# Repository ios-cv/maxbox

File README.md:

MaxBox open-source hardware
====================

This repository is for the 3D design files, KiCad PCB design/Gerber files, and ESP-IDF firmware files to produce a MaxBox control box. This takes the form of a 100mm diameter circular PCB with a Mifare antenna, buck converter capable of up to 36V DC input, RGB LEDs, high speed CAN bus transceiver, an ESP32-WROVER castellated module incorporating a Bluetooth and WiFi antenna, and GPIO to connect buttons and relays.

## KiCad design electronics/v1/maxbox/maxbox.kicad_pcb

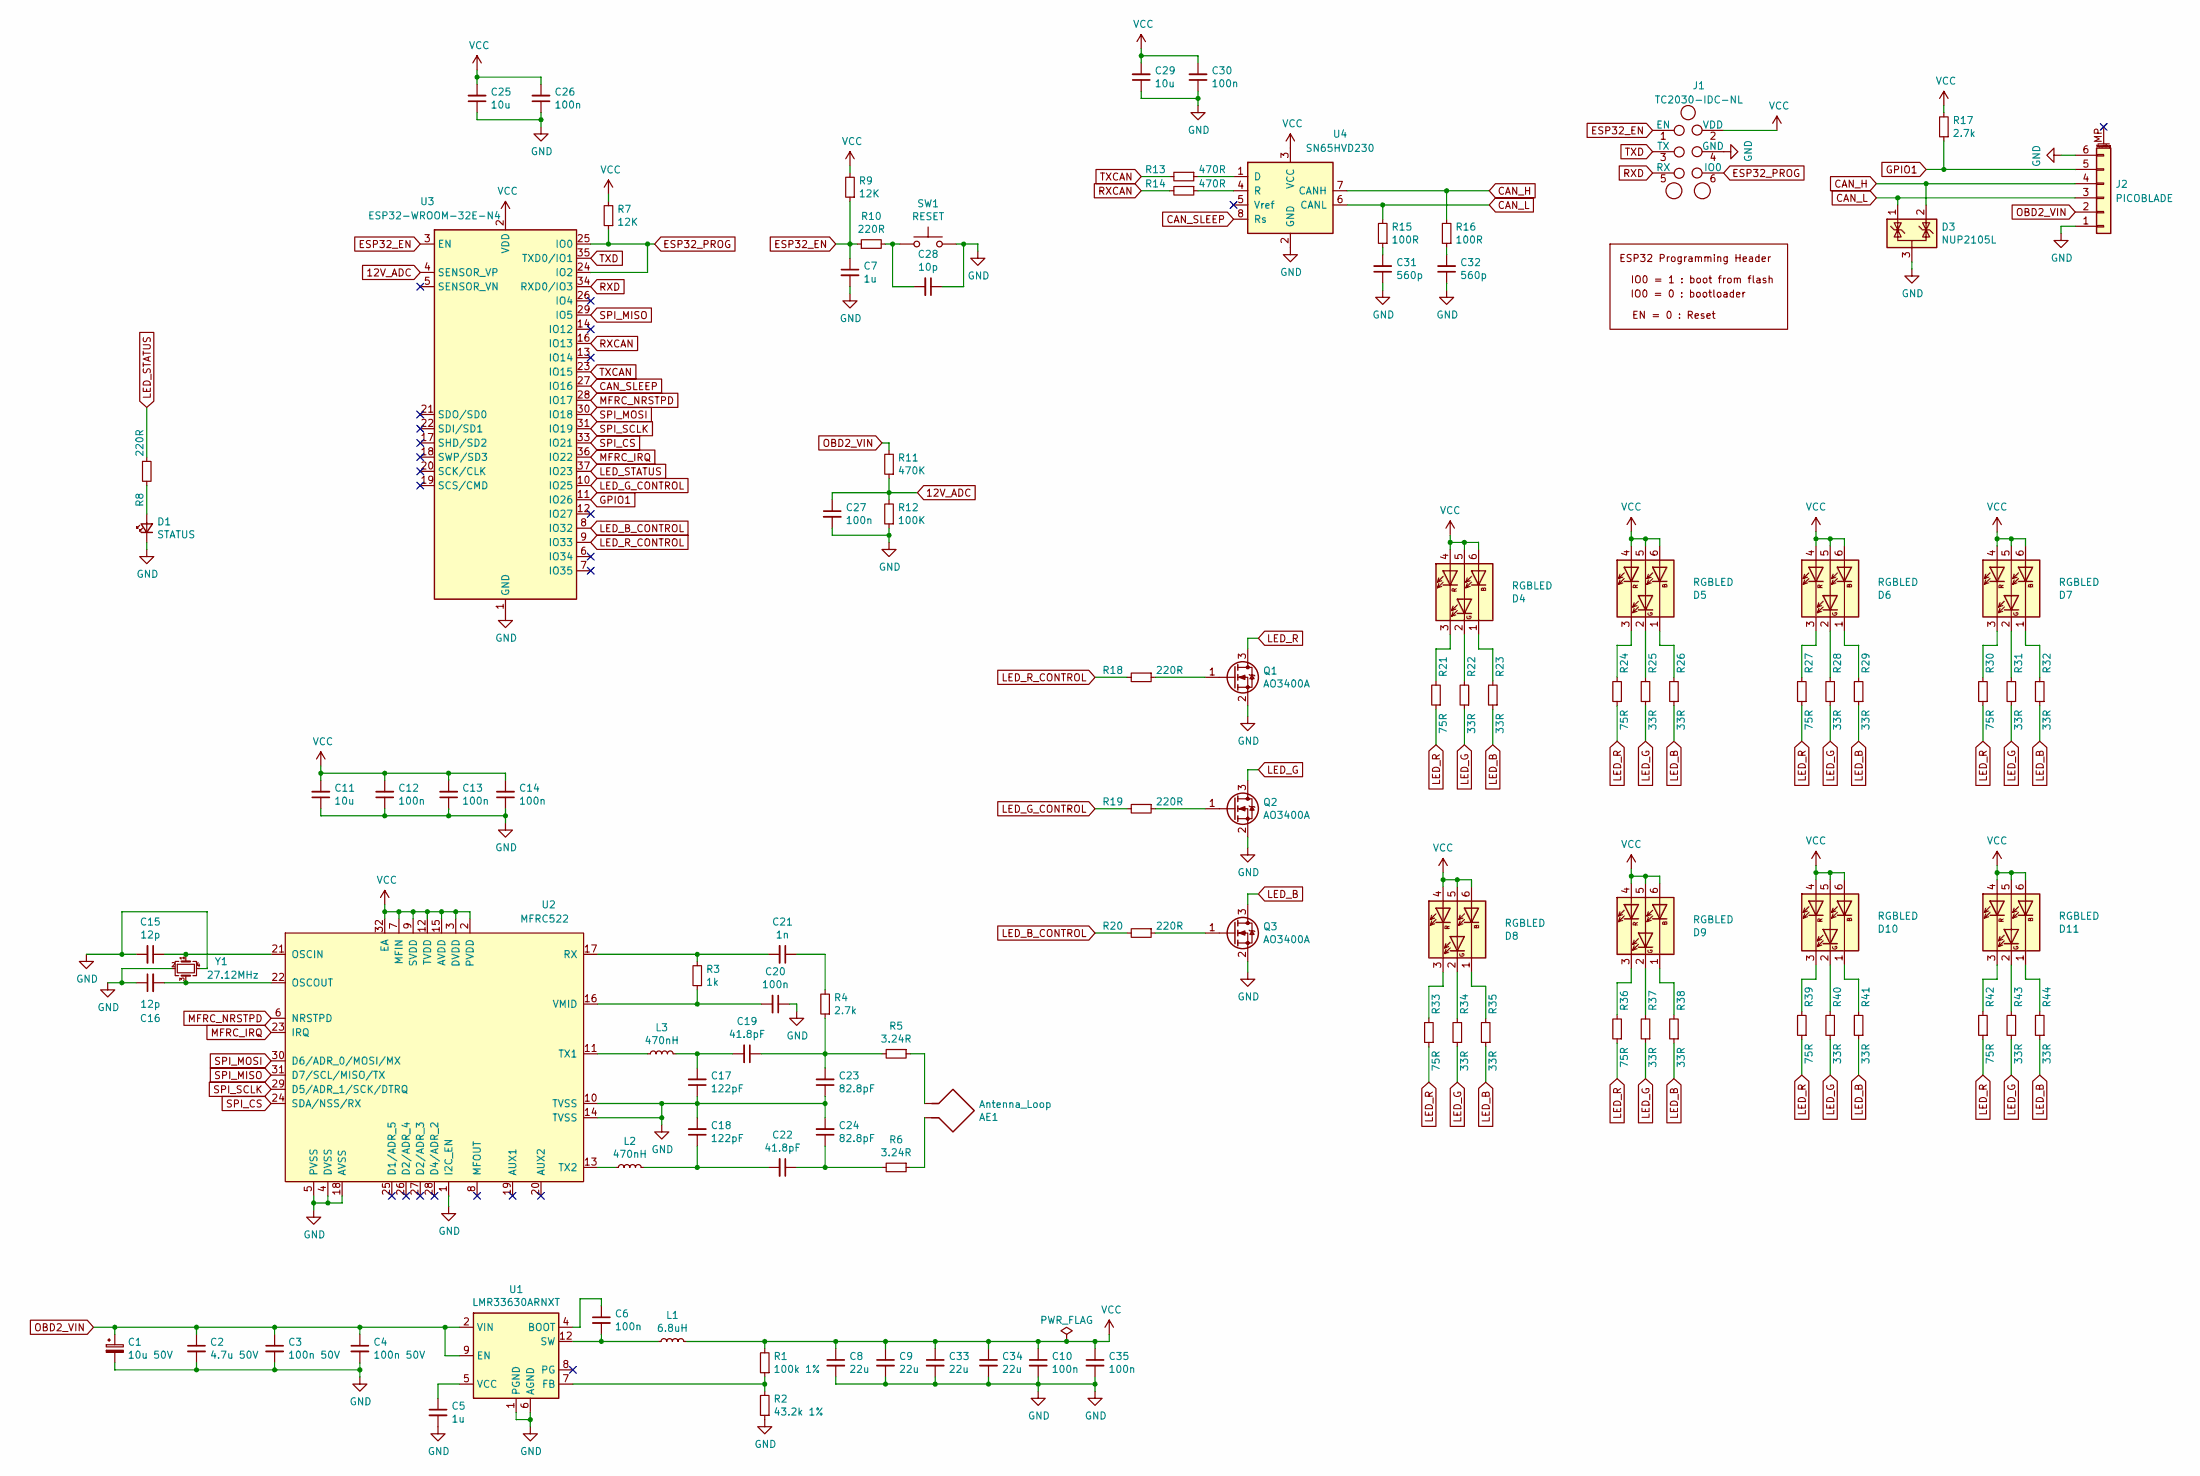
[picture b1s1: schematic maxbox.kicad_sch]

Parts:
AE1: Antenna_Loop; 95mm-3turn-antenna
C1: 10u 50V; C_0805_2012Metric; LCSC C440198
C2: 4.7u 50V; C_1206_3216Metric; LCSC C29823
C3, C4: 100n 50V; C_0402_1005Metric; LCSC C307331
C5, C7: 1u; C_0402_1005Metric; LCSC C52923
C6, C10, C12, C13, C14, C20, C26, C27, C30, C35: 100n; C_0402_1005Metric; LCSC C307331
C8, C9, C33, C34: 22u; C_0805_2012Metric; LCSC C45783
C11, C25, C29: 10u; C_0402_1005Metric; LCSC C15525
C15, C16: 12p; C_0805_2012Metric; LCSC C1792
C17, C18: 122pF; C_0603_1608Metric; LCSC C18438
C19, C22: 41.8pF; C_0805_2012Metric; LCSC C502147
C21: 1n; C_0402_1005Metric; LCSC C1523
C23, C24: 82.8pF; C_0805_2012Metric; LCSC C105942
C28: 10p; C_0402_1005Metric; LCSC C32949
C31, C32: 560p; C_0402_1005Metric; LCSC C1537
D1: STATUS; LED_0603_1608Metric; LCSC C72043
D3: NUP2105L; SOT-23; LCSC C284104
D4, D5, D6, D7, D8, D9, D10, D11: RGBLED; LED_FM-Z2727RGBA-SH; LCSC C727905
J1: TC2030-IDC-NL_ESP; Tag-Connect_TC2030-IDC-NL_2x03_P1.27mm_Vertical
J2: PICOBLADE; Molex_PicoBlade_53261-0671_1x06-1MP_P1.25mm_Horizontal; LCSC C99277
L1: 6.8uH; L_Cenker_CKST0603; LCSC C3002639
L2, L3: 470nH; L_0805_2012Metric; LCSC C655211
Q1, Q2, Q3: AO3400A; SOT-23; LCSC C20917
R1: 100k 1%; R_0402_1005Metric; LCSC C25741
R2: 43.2k 1%; R_0603_1608Metric; LCSC C23172
R3: 1k; R_0402_1005Metric; LCSC C11702
R4, R17: 2.7k; R_0603_1608Metric; LCSC C13167
R5, R6: 3.24R; R_0402_1005Metric; LCSC C270612
R7, R9: 12K; R_0402_1005Metric; LCSC C25752
R8, R10, R18, R19, R20: 220R; R_0402_1005Metric; LCSC C25091
R11: 470K; R_0402_1005Metric; LCSC C25790
R12: 100K; R_0402_1005Metric; LCSC C25741
R13, R14: 470R; R_0402_1005Metric; LCSC C25117
R15, R16: 100R; R_0402_1005Metric; LCSC C25076
R21, R24, R27, R30, R33, R36, R39, R42: 75R; R_0402_1005Metric; LCSC C25133
R22, R23, R25, R26, R28, R29, R31, R32, R34, R35, R37, R38, R40, R41, R43, R44: 33R; R_0402_1005Metric; LCSC C25105
SW1: RESET; XKB_TS-1187A-B-A-B; LCSC C318884
U1: LMR33630ARNXT; RNX0012B_VQFN-HR; LCSC C2861505
U2: MFRC522; VQFN-32-1EP_5x5mm_P0.5mm_EP3.5x3.5mm_ThermalVias; LCSC C11322
U3: ESP32-WROOM-32E-N4; ESP32-WROOM-32; LCSC C701341
U4: SN65HVD230; SOIC-8_3.9x4.9mm_P1.27mm; LCSC C12084
Y1: 27.12MHz; Crystal_SMD_3225-4Pin_3.2x2.5mm; LCSC C113669

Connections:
12V_ADC: C27.1, R11.1, R12.2, U3.4 (SENSOR_VP)
CAN_H: D3.2 (K), J2.4, R16.2, U4.7 (CANH)
CAN_L: D3.1 (K), J2.3, R15.2, U4.6 (CANL)
CAN_SLEEP: U3.27 (IO16), U4.8 (Rs)
ESP32_EN: C7.1, J1.1 (EN), R9.1, R10.1, U3.3 (EN)
ESP32_PROG: J1.6 (IO0), R7.1, U3.24 (IO2), U3.25 (IO0)
GND: C1.2, C2.2, C3.2, C4.2, C5.2, C7.2, C8.2, C9.2, C10.2, C11.1, C12.1, C13.1, C14.1, C15.2, C16.1, C17.1, C18.2, C20.1, C23.1, C24.2, C25.1, C26.1, C27.2, C28.1, C29.1, C30.1, C31.1, C32.1, C33.2, C34.2, C35.2, D1.1 (K), D3.3 (A), J1.4 (GND), J2.1, J2.6, Q1.2 (S), Q2.2 (S), Q3.2 (S), R2.1, R12.1, SW1.2, U1.1 (PGND), U1.6 (AGND), U1.11 (PGND), U2.1 (I2C_EN), U2.4 (DVSS), U2.5 (PVSS), U2.10 (TVSS), U2.14 (TVSS), U2.18 (AVSS), U3.1 (GND), U3.15 (GND), U3.38 (GND), U3.39 (GND), U4.2 (GND), Y1.2, Y1.4
GPIO1: J2.5, R17.1, U3.11 (IO26)
LED_B: Q3.3 (D), R23.1, R26.1, R29.1, R32.1, R35.1, R38.1, R41.1, R44.1
LED_B_CONTROL: R20.2, U3.8 (IO32)
LED_G: Q2.3 (D), R22.1, R25.1, R28.1, R31.1, R34.1, R37.1, R40.1, R43.1
LED_G_CONTROL: R19.2, U3.10 (IO25)
LED_R: Q1.3 (D), R21.1, R24.1, R27.1, R30.1, R33.1, R36.1, R39.1, R42.1
LED_R_CONTROL: R18.2, U3.9 (IO33)
LED_STATUS: R8.1, U3.37 (IO23)
MFRC_IRQ: U2.23 (IRQ), U3.36 (IO22)
MFRC_NRSTPD: U2.6 (NRSTPD), U3.28 (IO17)
unnamed: AE1.1, R6.1
unnamed: AE1.2, R5.1
unnamed: C5.1, U1.5 (VCC)
unnamed: C6.1, U1.4 (BOOT)
unnamed: C6.2, L1.1, U1.3 (NC), U1.12 (SW)
unnamed: C15.1, U2.21 (OSCIN), Y1.1
unnamed: C16.2, U2.22 (OSCOUT), Y1.3
unnamed: C17.2, C19.2, L3.2
unnamed: C18.1, C22.2, L2.2
unnamed: C19.1, C23.2, R4.1, R5.2
unnamed: C20.2, R3.1, U2.16 (VMID)
unnamed: C21.1, R4.2
unnamed: C21.2, R3.2, U2.17 (RX)
unnamed: C22.1, C24.1, R6.2
unnamed: C28.2, R10.2, SW1.1
unnamed: C31.2, R15.1
unnamed: C32.2, R16.1
unnamed: D1.2 (A), R8.2
unnamed: D4.1 (KB), R23.2
unnamed: D4.2 (KG), R22.2
unnamed: D4.3 (KR), R21.2
unnamed: D5.1 (KB), R26.2
unnamed: D5.2 (KG), R25.2
unnamed: D5.3 (KR), R24.2
unnamed: D6.1 (KB), R29.2
unnamed: D6.2 (KG), R28.2
unnamed: D6.3 (KR), R27.2
unnamed: D7.1 (KB), R32.2
unnamed: D7.2 (KG), R31.2
unnamed: D7.3 (KR), R30.2
unnamed: D8.1 (KB), R35.2
unnamed: D8.2 (KG), R34.2
unnamed: D8.3 (KR), R33.2
unnamed: D9.1 (KB), R38.2
unnamed: D9.2 (KG), R37.2
unnamed: D9.3 (KR), R36.2
unnamed: D10.1 (KB), R41.2
unnamed: D10.2 (KG), R40.2
unnamed: D10.3 (KR), R39.2
unnamed: D11.1 (KB), R44.2
unnamed: D11.2 (KG), R43.2
unnamed: D11.3 (KR), R42.2
unnamed: L2.1, U2.13 (TX2)
unnamed: L3.1, U2.11 (TX1)
unnamed: Q1.1 (G), R18.1
unnamed: Q2.1 (G), R19.1
unnamed: Q3.1 (G), R20.1
unnamed: R1.1, R2.2, U1.7 (FB)
unnamed: R13.1, U4.1 (D)
unnamed: R14.1, U4.4 (R)
OBD2_VIN: C1.1, C2.1, C3.1, C4.1, J2.2, R11.2, U1.2 (VIN), U1.9 (EN), U1.10 (VIN)
RXCAN: R14.2, U3.16 (IO13)
RXD: J1.5 (RX), U3.34 (RXD0/IO3)
SPI_CS: U2.24 (SDA/NSS/RX), U3.33 (IO21)
SPI_MISO: U2.31 (D7/SCL/MISO/TX), U3.29 (IO5)
SPI_MOSI: U2.30 (D6/ADR_0/MOSI/MX), U3.30 (IO18)
SPI_SCLK: U2.29 (D5/ADR_1/SCK/DTRQ), U3.31 (IO19)
TXCAN: R13.2, U3.23 (IO15)
TXD: J1.3 (TX), U3.35 (TXD0/IO1)
VCC: C8.1, C9.1, C10.1, C11.2, C12.2, C13.2, C14.2, C25.2, C26.2, C29.2, C30.2, C33.1, C34.1, C35.1, D4.4 (AR), D4.5 (AG), D4.6 (AB), D5.4 (AR), D5.5 (AG), D5.6 (AB), D6.4 (AR), D6.5 (AG), D6.6 (AB), D7.4 (AR), D7.5 (AG), D7.6 (AB), D8.4 (AR), D8.5 (AG), D8.6 (AB), D9.4 (AR), D9.5 (AG), D9.6 (AB), D10.4 (AR), D10.5 (AG), D10.6 (AB), D11.4 (AR), D11.5 (AG), D11.6 (AB), J1.2 (VDD), L1.2, R1.2, R7.2, R9.2, R17.2, U2.2 (PVDD), U2.3 (DVDD), U2.7 (MFIN), U2.9 (SVDD), U2.12 (TVDD), U2.15 (AVDD), U2.32 (EA), U3.2 (VDD), U4.3 (VCC)

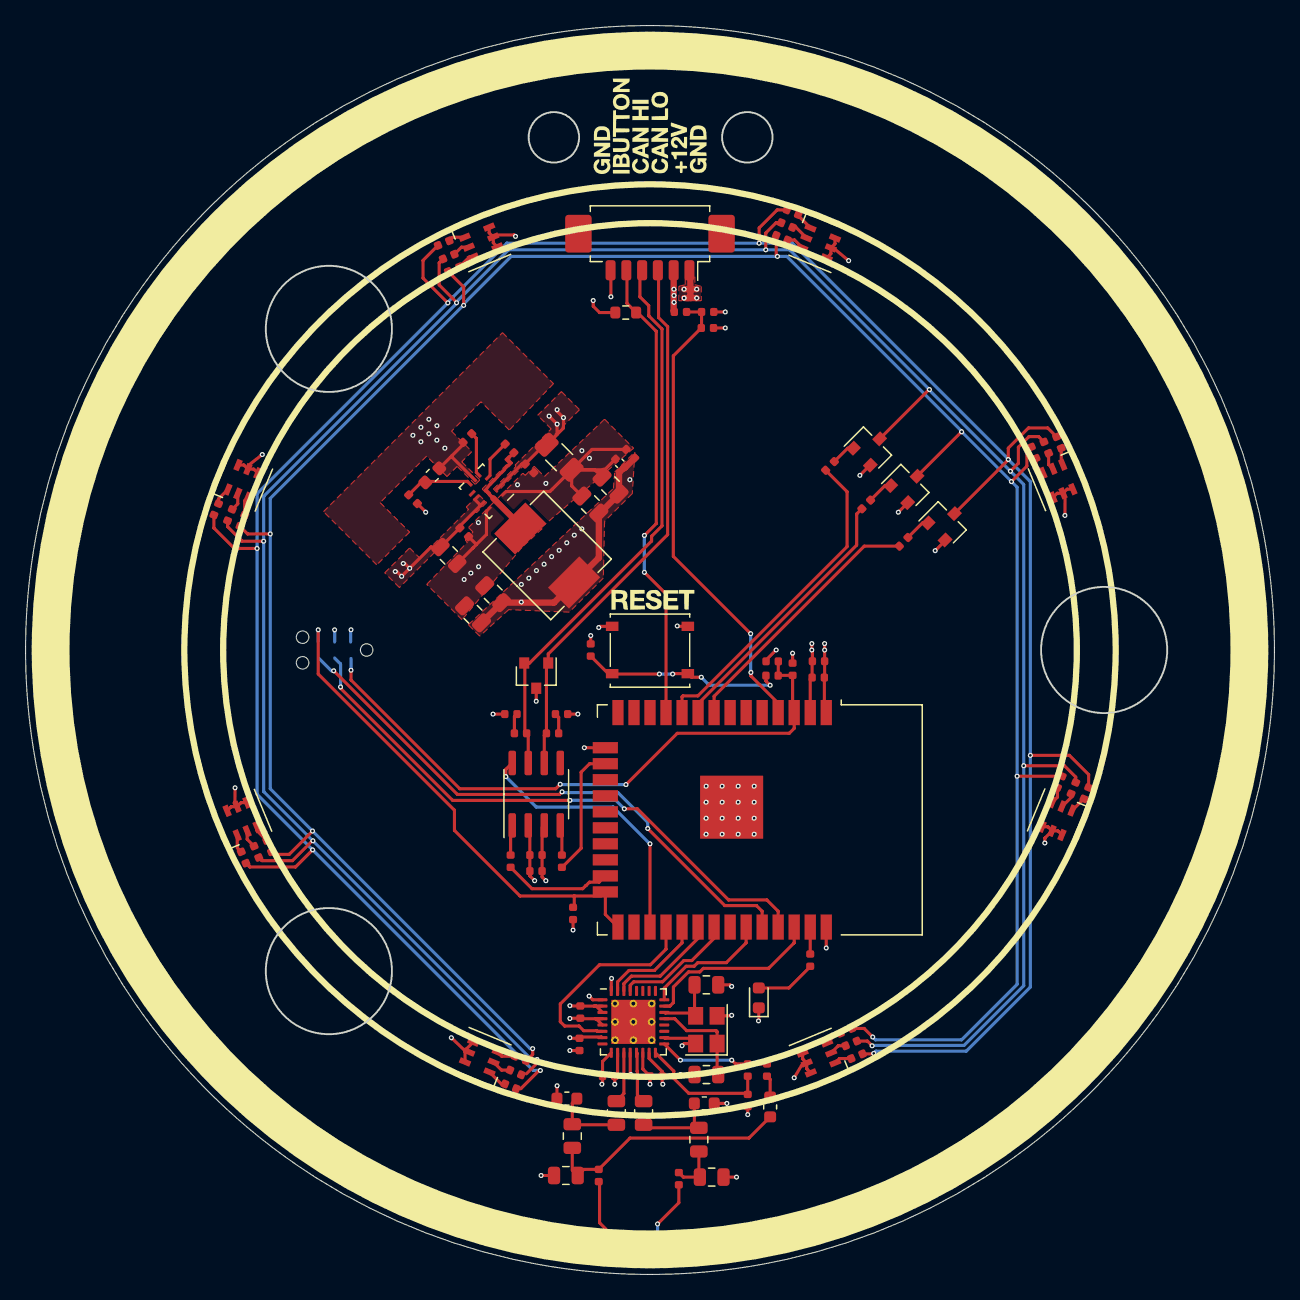
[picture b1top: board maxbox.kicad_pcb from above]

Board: 4 copper layers, 98.9 x 98.9 mm, 104 parts (1 on the bottom side), 77 nets.

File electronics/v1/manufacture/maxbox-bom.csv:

Comment,Designator,Footprint,LCSC
"10u 50V","C1","Capacitor_SMD:C_0805_2012Metric","C440198"
"10u","C11,C25,C29","Capacitor_SMD:C_0402_1005Metric","C15525"
"12p","C15,C16","Capacitor_SMD:C_0805_2012Metric","C1792"
"122pF","C17,C18","Capacitor_SMD:C_0603_1608Metric","C18438"
"41.8pF","C19,C22","Capacitor_SMD:C_0805_2012Metric","C502147"
"4.7u 50V","C2","Capacitor_SMD:C_1206_3216Metric","C29823"
"1n","C21","Capacitor_SMD:C_0402_1005Metric","C1523"
"82.8pF","C23,C24","Capacitor_SMD:C_0805_2012Metric","C105942"
"10p","C28","Capacitor_SMD:C_0402_1005Metric","C32949"
"100n 50V","C3,C4","Capacitor_SMD:C_0402_1005Metric","C307331"
"560p","C31,C32","Capacitor_SMD:C_0402_1005Metric","C1537"
"1u","C5,C7","Capacitor_SMD:C_0402_1005Metric","C52923"
"100n","C6,C10,C12,C13,C14,C20,C26,C27,C30,C35","Capacitor_SMD:C_0402_1005Metric","C307331"
"22u","C8,C9,C33,C34","Capacitor_SMD:C_0805_2012Metric","C45783"
"STATUS","D1","LED_SMD:LED_0603_1608Metric","C72043"
"NUP2105L","D3","Package_TO_SOT_SMD:SOT-23","C284104"
"RGBLED","D4,D5,D6,D7,D8,D9,D10,D11","maxlibrary:LED_FM-Z2727RGBA-SH","C727905"
"TC2030-IDC-NL_ESP","J1","Connector:Tag-Connect_TC2030-IDC-NL_2x03_P1.27mm_Vertical",""
"PICOBLADE","J2","Connector_Molex:Molex_PicoBlade_53261-0671_1x06-1MP_P1.25mm_Horizontal","C99277"
"6.8uH","L1","maxlibrary:L_Cenker_CKST0603","C3002639"
"470nH","L2,L3","Inductor_SMD:L_0805_2012Metric","C655211"
"AO3400A","Q1,Q2,Q3","Package_TO_SOT_SMD:SOT-23","C20917"
"100k 1%","R1","Resistor_SMD:R_0402_1005Metric","C25741"
"470K","R11","Resistor_SMD:R_0402_1005Metric","C25790"
"100K","R12","Resistor_SMD:R_0402_1005Metric","C25741"
"470R","R13,R14","Resistor_SMD:R_0402_1005Metric","C25117"
"100R","R15,R16","Resistor_SMD:R_0402_1005Metric","C25076"
"43.2k 1%","R2","Resistor_SMD:R_0603_1608Metric","C23172"
"75R","R21,R24,R27,R30,R33,R36,R39,R42","Resistor_SMD:R_0402_1005Metric","C25133"
"33R","R22,R23,R25,R26,R28,R29,R31,R32,R34,R35,R37,R38,R40,R41,R43,R44","Resistor_SMD:R_0402_1005Metric","C25105"
"1k","R3","Resistor_SMD:R_0402_1005Metric","C11702"
"2.7k","R4,R17","Resistor_SMD:R_0603_1608Metric","C13167"
"3.24R","R5,R6","Resistor_SMD:R_0402_1005Metric","C270612"
"12K","R7,R9","Resistor_SMD:R_0402_1005Metric","C25752"
"220R","R8,R10,R18,R19,R20","Resistor_SMD:R_0402_1005Metric","C25091"
"RESET","SW1","maxlibrary:XKB_TS-1187A-B-A-B","C318884"
"LMR33630ARNXT","U1","maxlibrary:RNX0012B_VQFN-HR","C2861505"
"MFRC522","U2","Package_DFN_QFN:VQFN-32-1EP_5x5mm_P0.5mm_EP3.5x3.5mm_ThermalVias","C11322"
"ESP32-WROOM-32E-N4","U3","RF_Module:ESP32-WROOM-32","C701341"
"SN65HVD230","U4","Package_SO:SOIC-8_3.9x4.9mm_P1.27mm","C12084"
"27.12MHz","Y1","Crystal:Crystal_SMD_3225-4Pin_3.2x2.5mm","C113669"

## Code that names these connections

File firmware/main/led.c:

#include "freertos/FreeRTOS.h"
#include "freertos/task.h"

#include "driver/gpio.h"
#include "led.h"

#define LED_R_PIN       33
#define LED_G_PIN       25
#define LED_B_PIN       32

#define LED_STATUS_PIN  23

led_status_t led_status = IDLE;

void led_init(void)
{
    // RGB LED pins should all be pulled low.
    gpio_set_direction(LED_R_PIN, GPIO_MODE_OUTPUT);
    gpio_set_direction(LED_G_PIN, GPIO_MODE_OUTPUT);
    gpio_set_direction(LED_B_PIN, GPIO_MODE_OUTPUT);
    gpio_set_direction(LED_STATUS_PIN, GPIO_MODE_OUTPUT);

    // LED init flash to indicate successful boot
    gpio_set_level(LED_R_PIN, 1);
    gpio_set_level(LED_G_PIN, 0);
    gpio_set_level(LED_B_PIN, 0);
    vTaskDelay(pdMS_TO_TICKS(200));
    gpio_set_level(LED_R_PIN, 0);
    gpio_set_level(LED_G_PIN, 1);
    gpio_set_level(LED_B_PIN, 0);
    vTaskDelay(pdMS_TO_TICKS(200));
    gpio_set_level(LED_R_PIN, 0);
    gpio_set_level(LED_G_PIN, 0);
    gpio_set_level(LED_B_PIN, 1);
    vTaskDelay(pdMS_TO_TICKS(200));
    gpio_set_level(LED_B_PIN, 0);
}

void led_update(led_status_t st)
{
    led_status = st;
}

void led_loop(void *args)
{
    while (true)
    {
        uint64_t ms_elapsed = xTaskGetTickCount()*portTICK_PERIOD_MS;

        if(led_status == IDLE)
        {
            gpio_set_level(LED_R_PIN,0);
            gpio_set_level(LED_G_PIN,0);
            gpio_set_level(LED_B_PIN,0);
            gpio_set_level(LED_STATUS_PIN, 0);

        }
        else if(led_status == HEARTBEAT)
        {
            gpio_set_level(LED_R_PIN,0);
            gpio_set_level(LED_G_PIN,0);
            gpio_set_level(LED_B_PIN,0);
            gpio_set_level(LED_STATUS_PIN, 1);
            led_update(IDLE); // only want this for one LED tick
        }
        else if(led_status == PROCESSING)
        {
            gpio_set_level(LED_R_PIN,1);
            gpio_set_level(LED_G_PIN,1);
            gpio_set_level(LED_B_PIN,1);
        }
        else if(led_status == DENY)
        {
            gpio_set_level(LED_R_PIN,1);
            gpio_set_level(LED_G_PIN,0);
            gpio_set_level(LED_B_PIN,0); 
        }
        else if(led_status == ERROR)
        {
            if (ms_elapsed % 500 >= 250)
            {
            gpio_set_level(LED_R_PIN,1);
            gpio_set_level(LED_G_PIN,0);
            gpio_set_level(LED_B_PIN,0); 
            }
            else
            {
            gpio_set_level(LED_R_PIN,0);
            gpio_set_level(LED_G_PIN,0);
            gpio_set_level(LED_B_PIN,0);    
            }
        }
        else if(led_status == LOCKING)
        {
            gpio_set_level(LED_R_PIN,0);
            gpio_set_level(LED_G_PIN,1);
            gpio_set_level(LED_B_PIN,0);

        }
        else if(led_status == UNLOCKING)
        {
            gpio_set_level(LED_R_PIN,0);
            gpio_set_level(LED_G_PIN,0);
            gpio_set_level(LED_B_PIN,1);
        }
        else if(led_status == FIRMWARE)
        {
            if (ms_elapsed % 1000 >= 500)
            {
            gpio_set_level(LED_R_PIN,1);
            gpio_set_level(LED_G_PIN,1);
            gpio_set_level(LED_B_PIN,0);
            }
            else
            {
            gpio_set_level(LED_R_PIN,0);
            gpio_set_level(LED_G_PIN,1);
            gpio_set_level(LED_B_PIN,1);
            }
        }
        vTaskDelay(pdMS_TO_TICKS(20));
        }

        vTaskDelete(NULL);

}

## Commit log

2023-02-06 Initial clean commit for public v1 release.
